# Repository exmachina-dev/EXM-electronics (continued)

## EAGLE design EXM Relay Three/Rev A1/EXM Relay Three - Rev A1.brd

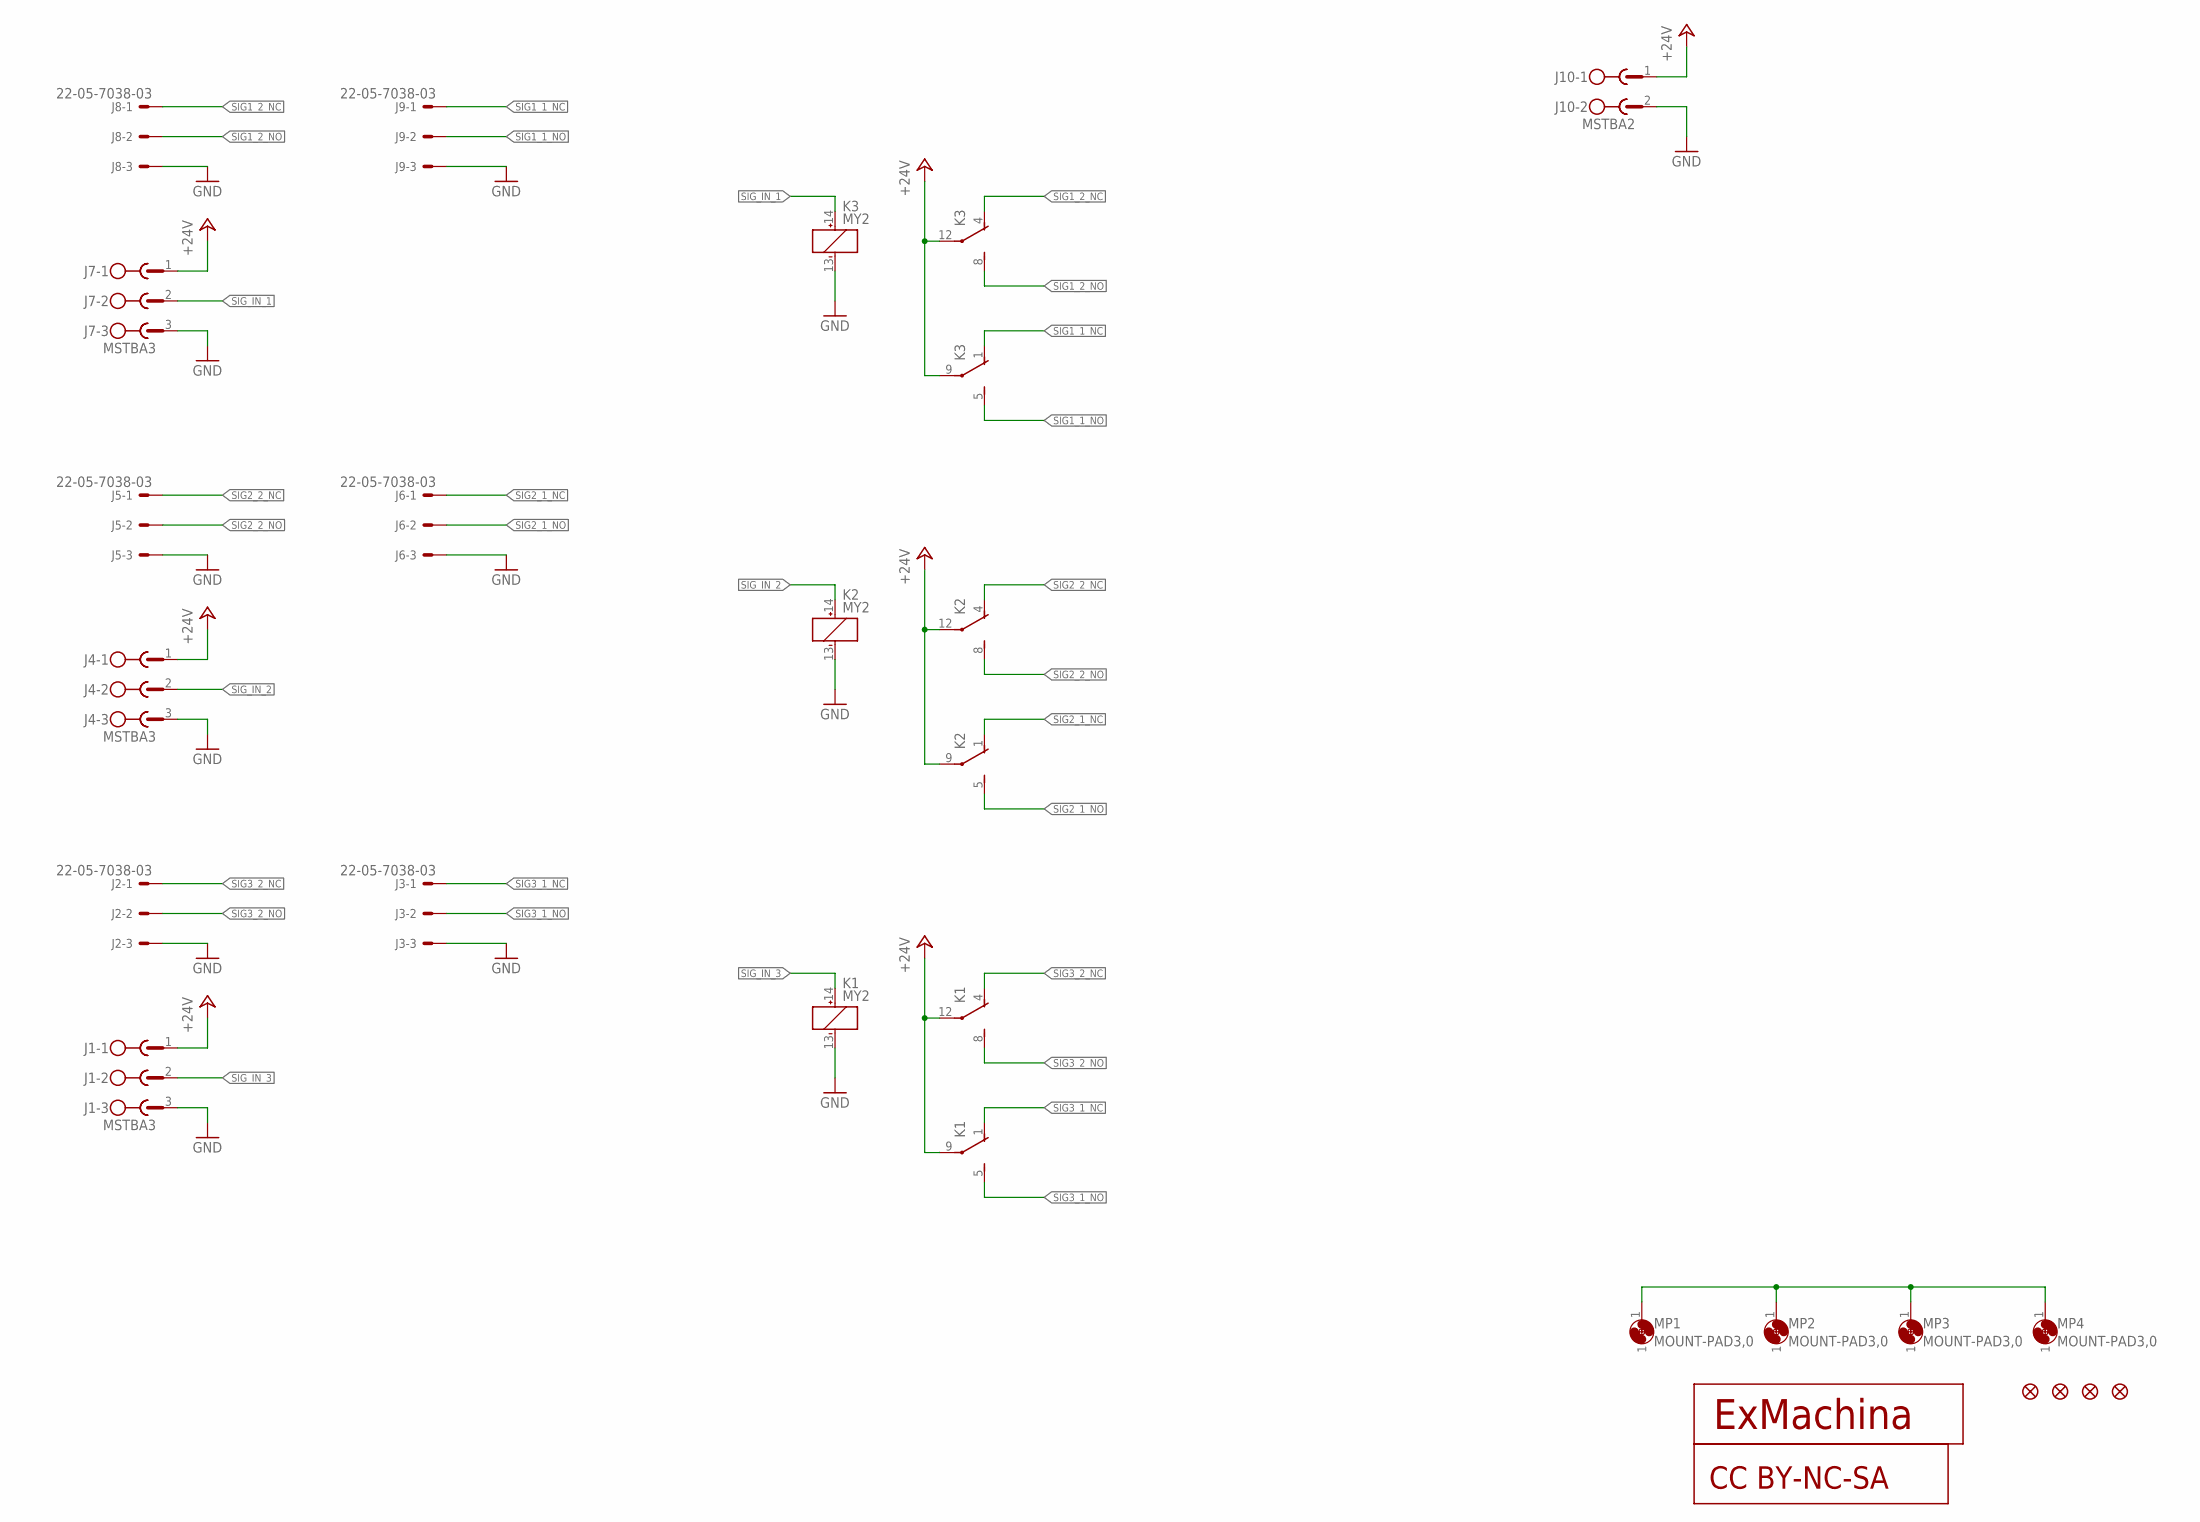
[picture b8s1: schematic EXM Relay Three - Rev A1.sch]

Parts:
CC1: CC-BY-NC-SA
J1, J4, J7: MSTBA3
J2, J3, J5, J6, J8, J9: 22-05-7038-03; 7395-03; MPN 22-05-7038
J10: MSTBA2
JP1, JP2, JP3, JP4: FIDUCIAL1X2; FIDUCIAL-1X2
K1, K2, K3: MY2; PY08; MPN PY08
MP1, MP2, MP3, MP4: MOUNT-PAD3,0; P3,0
T1: EXMACHINA-LOGO-NAME; EXM-LOGO-BASELINE

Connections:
1: MP1.1, MP2.1, MP3.1, MP4.1
+24V: J1.1, J4.1, J7.1, J10.1, K1.9 (C), K1.12 (C), K2.9 (C), K2.12 (C), K3.9 (C), K3.12 (C)
GND: J1.3, J2.3, J3.3, J4.3, J5.3, J6.3, J7.3, J8.3, J9.3, J10.2, K1.13 (-), K2.13 (-), K3.13 (-)
SIG1_1_NC: J9.1, K3.1 (NC)
SIG1_1_NO: J9.2, K3.5 (NO)
SIG1_2_NC: J8.1, K3.4 (NC)
SIG1_2_NO: J8.2, K3.8 (NO)
SIG2_1_NC: J6.1, K2.1 (NC)
SIG2_1_NO: J6.2, K2.5 (NO)
SIG2_2_NC: J5.1, K2.4 (NC)
SIG2_2_NO: J5.2, K2.8 (NO)
SIG3_1_NC: J3.1, K1.1 (NC)
SIG3_1_NO: J3.2, K1.5 (NO)
SIG3_2_NC: J2.1, K1.4 (NC)
SIG3_2_NO: J2.2, K1.8 (NO)
SIG_IN_1: J7.2, K3.14 (+)
SIG_IN_2: J4.2, K2.14 (+)
SIG_IN_3: J1.2, K1.14 (+)

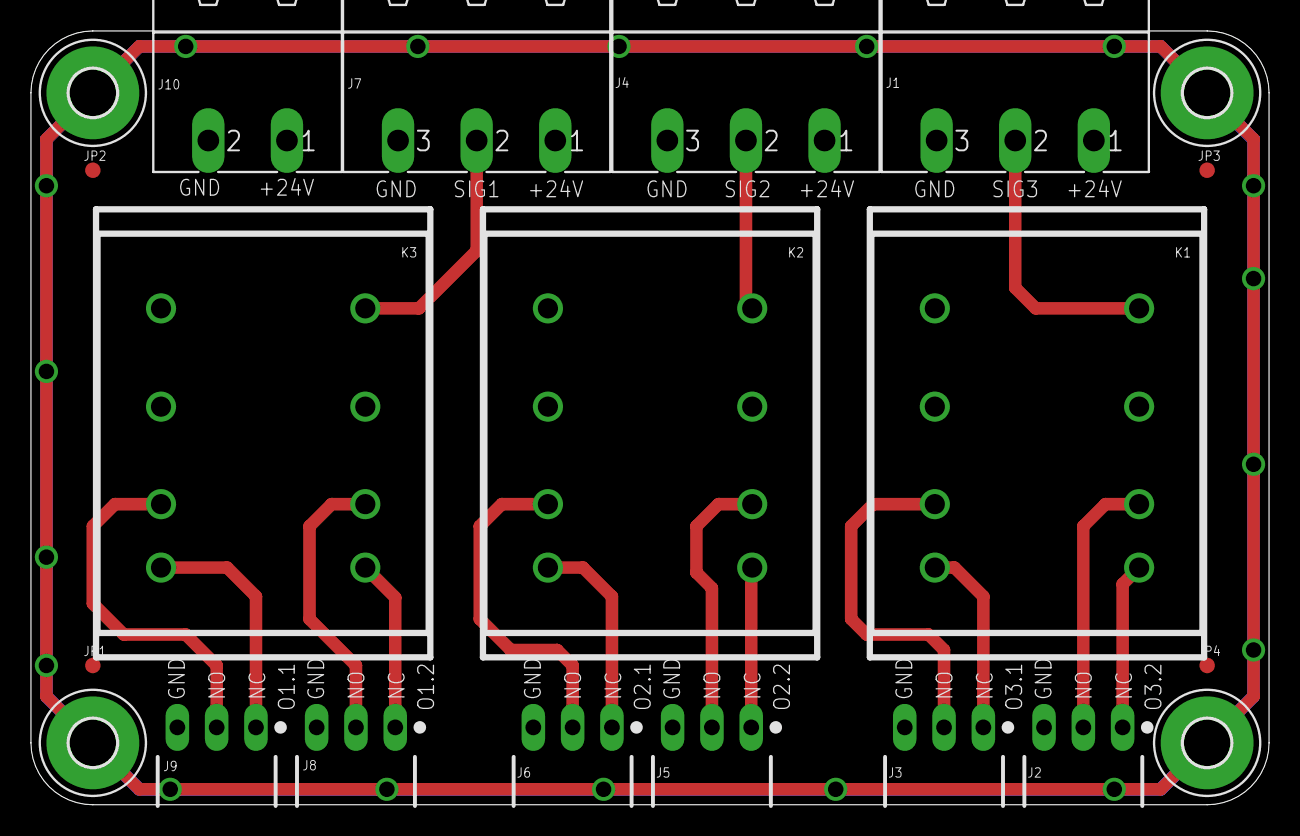
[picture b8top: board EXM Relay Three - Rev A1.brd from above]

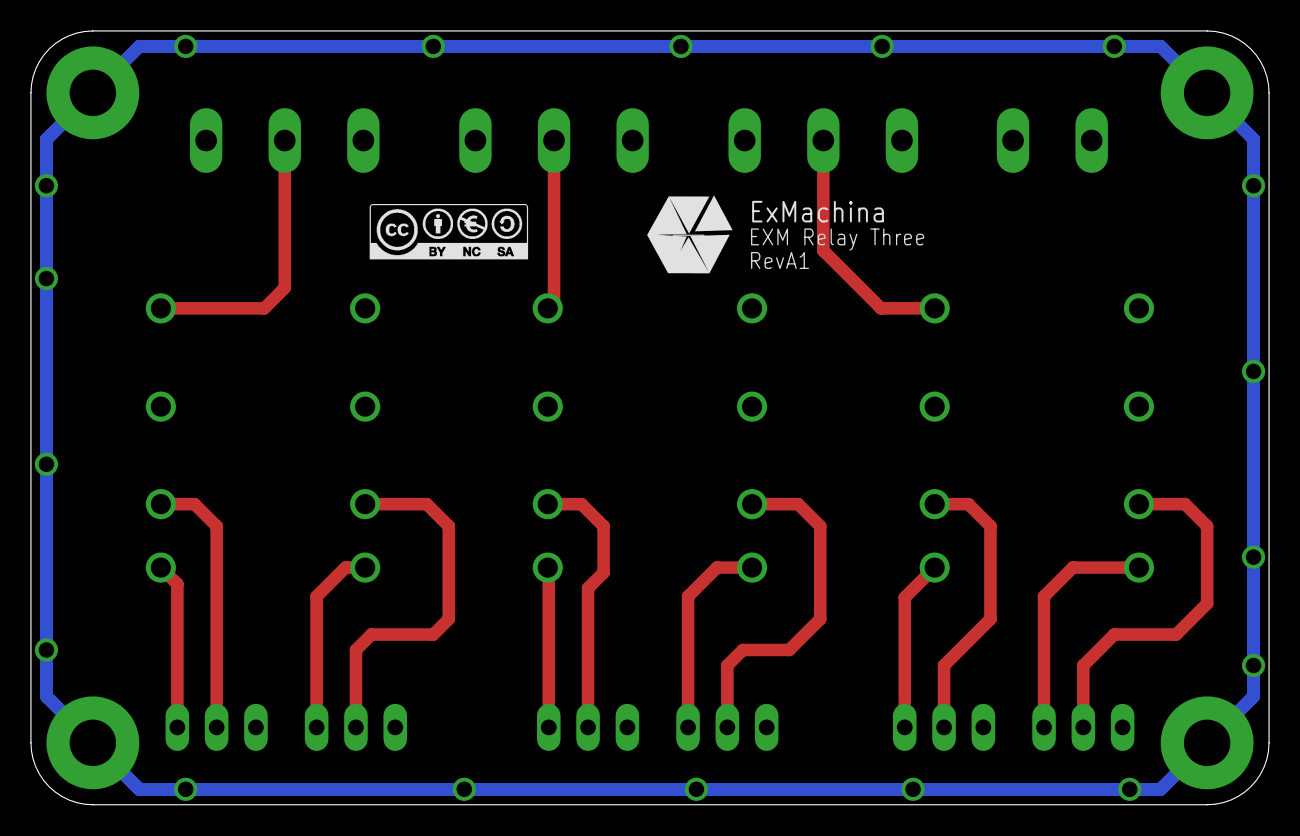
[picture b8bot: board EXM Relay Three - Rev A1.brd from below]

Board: 2 copper layers, 80.0 x 50.0 mm, 24 parts (2 on the bottom side), 18 nets.

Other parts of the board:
U$1: A4L-LOC

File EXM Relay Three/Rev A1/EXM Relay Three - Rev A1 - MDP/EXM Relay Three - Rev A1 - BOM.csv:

"Qty";"Value";"Device";"Package";"Parts";"Description";"MF";"MPN";"OC_FARNELL";"OC_NEWARK";
"6";"22-05-7038-03";"22-05-7038-03";"7395-03";"J2, J3, J5, J6, J8, J9";"CONNECTOR";"";"22-05-7038";"9731610 ";"26M6362";
"1";"CC-BY-NC-SA";"CC-BY-NC-SA";"CC-BY-NC-SA";"CC1";"";"";"";"";"unknown";
"1";"EXMACHINA-LOGO-NAME";"EXMACHINA-LOGO-NAME";"EXM-LOGO-BASELINE";"T1";"";"";"";"";"unknown";
"4";"FIDUCIAL1X2";"FIDUCIAL1X2";"FIDUCIAL-1X2";"JP1, JP2, JP3, JP4";"Fiducial Alignment Points";"";"";"";"unknown";
"4";"MOUNT-PAD3,0";"MOUNT-PAD3,0";"P3,0";"MP1, MP2, MP3, MP4";"MOUNTING HOLE with drill center marker";"";"";"";"unknown";
"1";"MSTBA2";"MSTBA2";"MSTBA2";"J10";"PHOENIX";"FARNELL";"1757242";"3705171";"71C4161";
"3";"MSTBA3";"MSTBA3";"MSTBA3";"J1, J4, J7";"PHOENIX";"FARNELL";"1757255";"3705183";"71C4162";
"3";"MY2";"MY2";"PY08";"K1, K2, K3";"";"OMRON COMPONENTS USA";"PY08";"";"36K3464";

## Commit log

2017-03-01 Clean repo
2017-03-01 Rename ArmazEthernet into SwitchEthernet
2017-03-01 Change description and create Switch-Ethernet Rev A3
2017-03-01 Update Description and Readme
2017-03-03 Rename .sch and .brd
2017-03-03 Preplace component on the board
2017-03-03 Connect board-to board connector
2017-03-07 Update connector and route eth 1,2 and 3
2017-03-07 Reroute ETH signals
2017-03-07 Route the spi nets
2017-03-08 Change to the top the RJ45 connector and re-route it
2017-03-08 change position of the resistors of neutrix connectors and re-route
2017-03-08 Route the board
2017-03-08 Route LED +5V
2017-03-09 Finish the routing
2017-03-13 Add bRestrict on the Neutrix panel and route GND nets
2017-04-24 Adjust connector possition and panelize the board
2017-04-25 Add via to the guard ring
2017-04-25 Connect GND meca of the connectors to the guard ring
2017-04-26 Add the cotation, the board name, the logo and the CC
2017-04-27 Adjut LED position on the board
2017-05-02 lear clearance on net and angle
2017-05-02 Replace J2 to femal connector and reroute the board, replace holes
2017-05-04 Modified the board according to the review
2017-05-04 Add operating voltage and consumption on silkscreen
2017-05-09 Rename guard ring on inner layer
2017-05-09 Update dimension layer
2017-05-09 Update silkscreen
2017-05-09 Fix keepout polygon on filters
2017-05-09 Update libraries and minor tweaks (keepouts)
2017-05-09 Fixed missing connection to GND
2017-05-09 Place name and value correctly on the board
2017-05-09 Create MDP folder and add placement top and bottom
2017-05-11 Generate MDP
2017-05-11 Replace device name on D2 and C3, C7, C19
2017-05-17 Add emergency stop board
2017-05-18 Modify power connector
2017-06-06 Finishing emergency stop board and generate MDP folder
2017-06-06 Archive gerber files and update BOM
2017-06-07 generate MDP folder
2017-06-07 Move JP4 and route the GND_MECA
2017-06-09 Generate BOM and gerber
2017-07-18 Add DMX proto board
2017-07-20 change dmx buffer
2017-07-20 Add power isolation to the schematic
2017-07-20 Add capsitor on the power
2017-07-21 Add Transint proction and name's net of the output
2017-08-03 Route the board and generate gerber
2017-10-06 Create Rev A2 of Emergency Stop board
2017-10-06 Update BOM
2017-10-06 Replace MSTBA with Molex headers and reroute
2017-10-06 Renamed dir and files (Emergency_Stop)
2017-10-09 Add MDP files
2017-10-13 Add BPtoJTAG_ICSP board files
2017-11-13 Add EmergencyStop - Rev A3 schematics and pcb design
2017-11-13 Update EmergencyStop - Rev A3
    - Fix layout
    - Major redesign in schematics
    - Add Lamp output
    - Add onboard led
2017-11-16 create EXM Relay one from eisla Armaz Relay
2017-11-16 Generate MDP files
2017-11-16 Generated Gerber files
2017-11-16 Create 3 relays board
2017-11-28 Change LED ethernet
2017-11-28 Clean repos + generated mechanical drawing
2017-11-28 Re-route the ethernet leds
2017-11-28 Update relay symbole and re-route the board
2017-11-28 Update relay device and re-route the board
2017-11-28 Rename .sch and .brd to relay three
2017-11-28 Clean the folder and repair .sch file
2017-11-28 Create EXM Relay four board
2017-12-06 Renumber outputs and change silkscreen
2017-12-06 Generate Gerber
2017-12-15 Create EXM HMI LED Rev A1 board
2017-12-15 Generated gerber
2017-12-15 Generated BOM files
2017-12-15 Create EXM Relay Three Rev A2, add C on each relay interface
2017-12-15 Renumber part and updated BOM
2017-12-15 Create EXM Encoder project
2017-12-15 Generated MDP files
2017-12-15 Finish to route the board
2017-12-18 Reorganization of schematic layouts
2017-12-18 Fix bad revision name on CPU board
2017-12-18 Don't mirror the layer identifier 2
2017-12-18 Update schematic and board due to the update of encoder symbol
2017-12-18 Add bottom silkscreen on EXM Encoder
2017-12-18 Update from libraries:
    - `con-molex`
    - `encoder.lbr`
2017-12-20 Create EXM Safety Stop board
2017-12-20 Generated Gerber of EXM HMI LED Rev A1
2017-12-21 Final revision before review:
    - Update package silkscreen
    - Reroute to prevent GND from being broke
    - Change signal trace width to 8mil
    - Change power trace width to 12mil
    - Connect FTDI +5V to converter instead of VDD
2017-12-22 Add LED dimensions
2017-12-22 Final modifications before MDP in EXM Safety board - Rev A1:
    - Renamed signal +24V_IN to +24V_PS
    - Named signal +24V_IN
    - Connect +24V_OUT after the fuse
2017-12-22 Change width for LED trace
2017-12-22 Update EXM - Safety Board - Rev A1 form libraries
2017-12-22 Renamed EXM Safety Stop to EXM Safety Board
2018-01-03 Generated MDP files of EXM Encoder Rev A1
2018-01-03 Switch Ethernet Rev A6 : Deplace some via and replace the fuse
2018-01-31 Generate MDP for BPtoJTAG_ISCP
2018-01-31 Add EXM Relay One rev A3
2018-01-31 generated MDP files of Ethernet switch rev A6
